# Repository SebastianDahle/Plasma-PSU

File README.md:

View this project on [CADLAB.io](https://cadlab.io/project/22638). 

# Plasma-PSU
Semi-professional HV power supply for various plasma applications, including Gliding Arcs, Dielectric Barrier Discharges, or School demonstrations. The design shall be suited for use in a laboratory environment, but simple and cheap to allow for uptake in DIY communities.

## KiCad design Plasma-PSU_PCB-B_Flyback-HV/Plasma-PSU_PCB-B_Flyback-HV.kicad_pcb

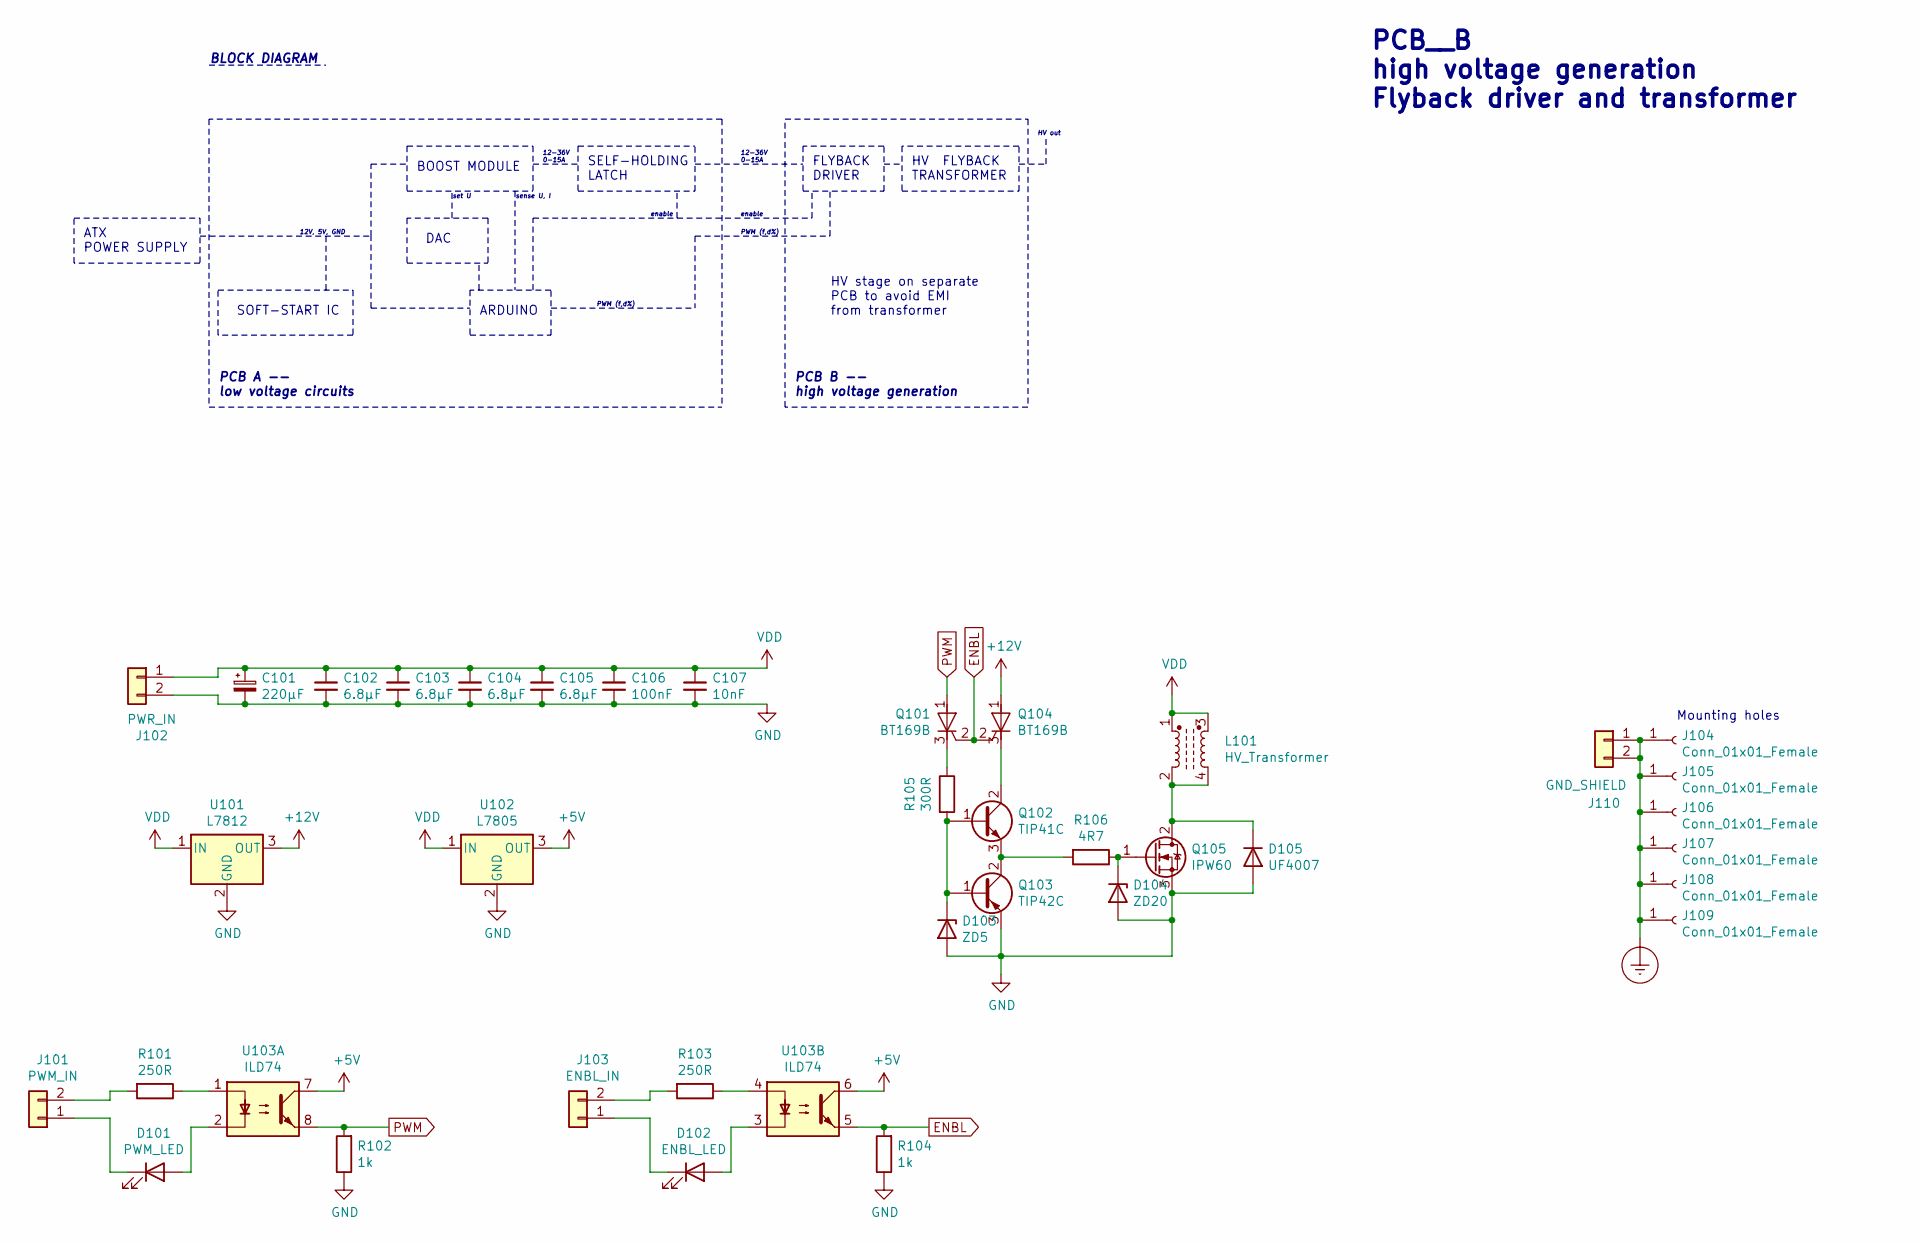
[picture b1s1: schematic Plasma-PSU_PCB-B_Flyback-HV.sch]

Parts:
C101: 220µF; CP_Radial_D8.0mm_P3.50mm
C102, C103, C104, C105: 6.8µF; C_Disc_D6.0mm_W2.5mm_P5.00mm
C106: 100nF; C_1206_3216Metric
C107: 10nF; C_0805_2012Metric
D101: PWM_LED; LED_0603_1608Metric
D102: ENBL_LED; LED_0603_1608Metric
D103: ZD5; D_DO-41_SOD81_P7.62mm_Horizontal
D104: ZD20; D_DO-41_SOD81_P7.62mm_Horizontal
D105: UF4007; D_DO-41_SOD81_P7.62mm_Horizontal
J101: PWM_IN; PinHeader_1x02_P2.54mm_Vertical
J102: PWR_IN; TerminalBlock_Phoenix_MKDS-3-2-5.08_1x02_P5.08mm_Horizontal
J103: ENBL_IN; PinHeader_1x02_P2.54mm_Vertical
J104, J105, J106, J107, J108, J109: Conn_01x01_Female; MountingHole_3.2mm_M3_Pad_Via
J110: GND_SHIELD; TerminalBlock_Phoenix_MKDS-3-2-5.08_1x02_P5.08mm_Horizontal
L101: HV_Transformer; HF-HV_Transformer_15kV_300W
Q101, Q104: BT169B; TO-92_Inline
Q102: TIP41C; TO-220-3_Vertical
Q103: TIP42C; TO-220-3_Vertical
Q105: IPW60; TO-247-3_Vertical
R101, R103: 250R; R_0603_1608Metric
R102, R104: 1k; R_0603_1608Metric
R105: 300R; R_0603_1608Metric
R106: 4R7; R_Axial_DIN0207_L6.3mm_D2.5mm_P7.62mm_Horizontal
U101: L7812; TO-220-3_Vertical
U102: L7805; TO-220-3_Vertical
U103: ILD74; DIP-8_W7.62mm

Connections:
+5V: U102.3 (OUT), U103.6, U103.7
+12V: Q104.1 (A), U101.3 (OUT)
ENBL: Q101.2 (G), Q104.2 (G), R104.2, U103.5
Earth_Protective: J104.1, J105.1, J106.1, J107.1, J108.1, J109.1, J110.1, J110.2
GND: C101.2, C102.2, C103.2, C104.2, C105.2, C106.2, C107.2, D103.2 (A), D104.2 (A), D105.2 (A), J102.2, Q103.3 (E), Q105.3 (S), R102.1, R104.1, U101.2 (GND), U102.2 (GND)
unnamed: D101.1 (K), J101.1
unnamed: D101.2 (A), U103.2
unnamed: D102.1 (K), J103.1
unnamed: D102.2 (A), U103.3
unnamed: D103.1 (K), Q102.1 (B), Q103.1 (B), R105.2
unnamed: D104.1 (K), Q105.1 (G), R106.1
unnamed: D105.1 (K), L101.2, L101.4, Q105.2 (D)
unnamed: J101.2, R101.2
unnamed: J103.2, R103.2
unnamed: Q101.3 (K), R105.1
unnamed: Q102.2 (C), Q104.3 (K)
unnamed: Q102.3 (E), Q103.2 (C), R106.2
unnamed: R101.1, U103.1
unnamed: R103.1, U103.4
PWM: Q101.1 (A), R102.2, U103.8
VDD: C101.1, C102.1, C103.1, C104.1, C105.1, C106.1, C107.1, J102.1, L101.1, L101.3, U101.1 (IN), U102.1 (IN)

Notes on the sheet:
HV stage on separate PCB to avoid EMI from transformer
PCB__B high voltage generation Flyback driver and transformer
ATX POWER SUPPLY
SOFT-START IC
BOOST MODULE
ARDUINO
DAC
FLYBACK DRIVER
HV FLYBACK TRANSFORMER
set U
sense U, I
12-36V 0-15A
PWM (f,d%)
HV out
PCB A -- low voltage circuits
PCB B -- high voltage generation
BLOCK DIAGRAM
SELF-HOLDING LATCH
enable
12V, 5V, GND
Mounting holes

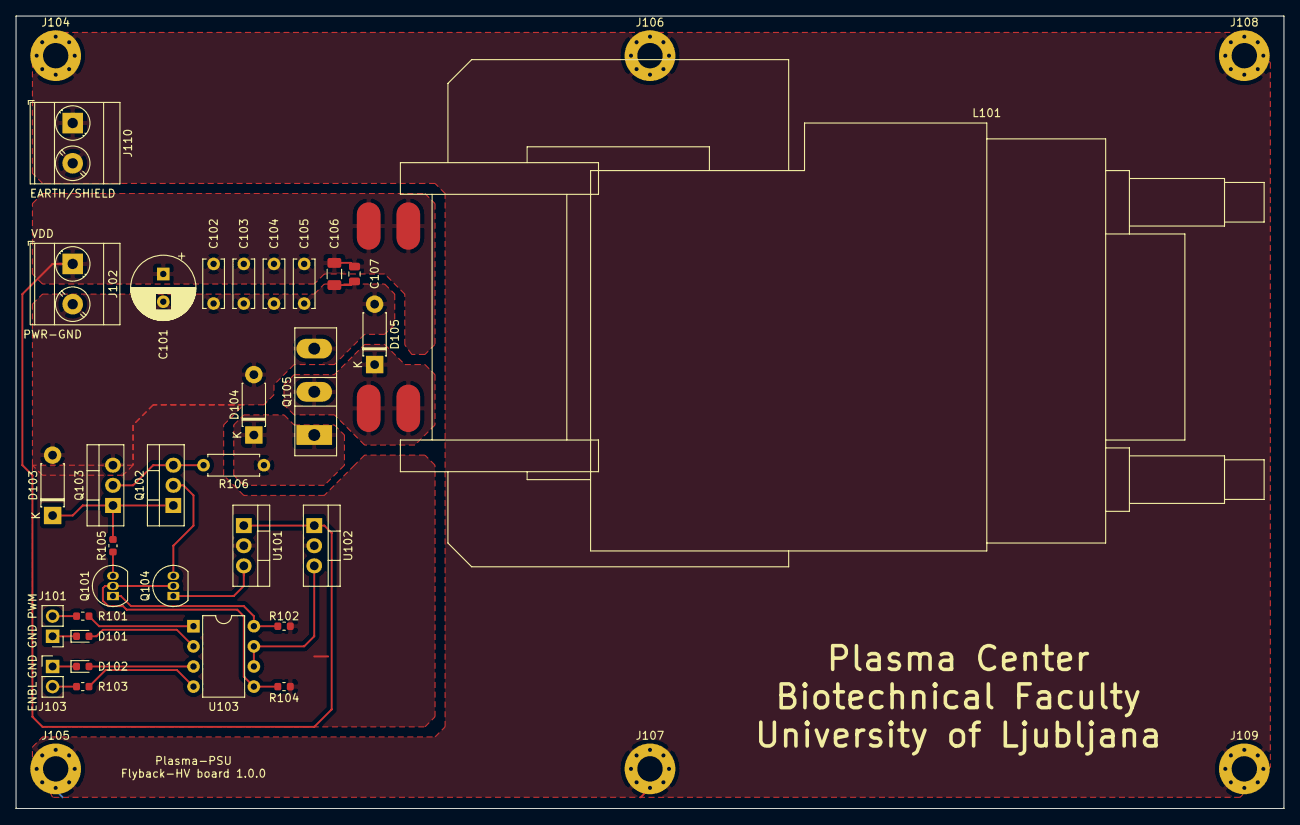
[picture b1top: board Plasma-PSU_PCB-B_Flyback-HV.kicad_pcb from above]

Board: 2 copper layers, 160.0 x 100.0 mm, 37 parts (0 on the bottom side), 21 nets.

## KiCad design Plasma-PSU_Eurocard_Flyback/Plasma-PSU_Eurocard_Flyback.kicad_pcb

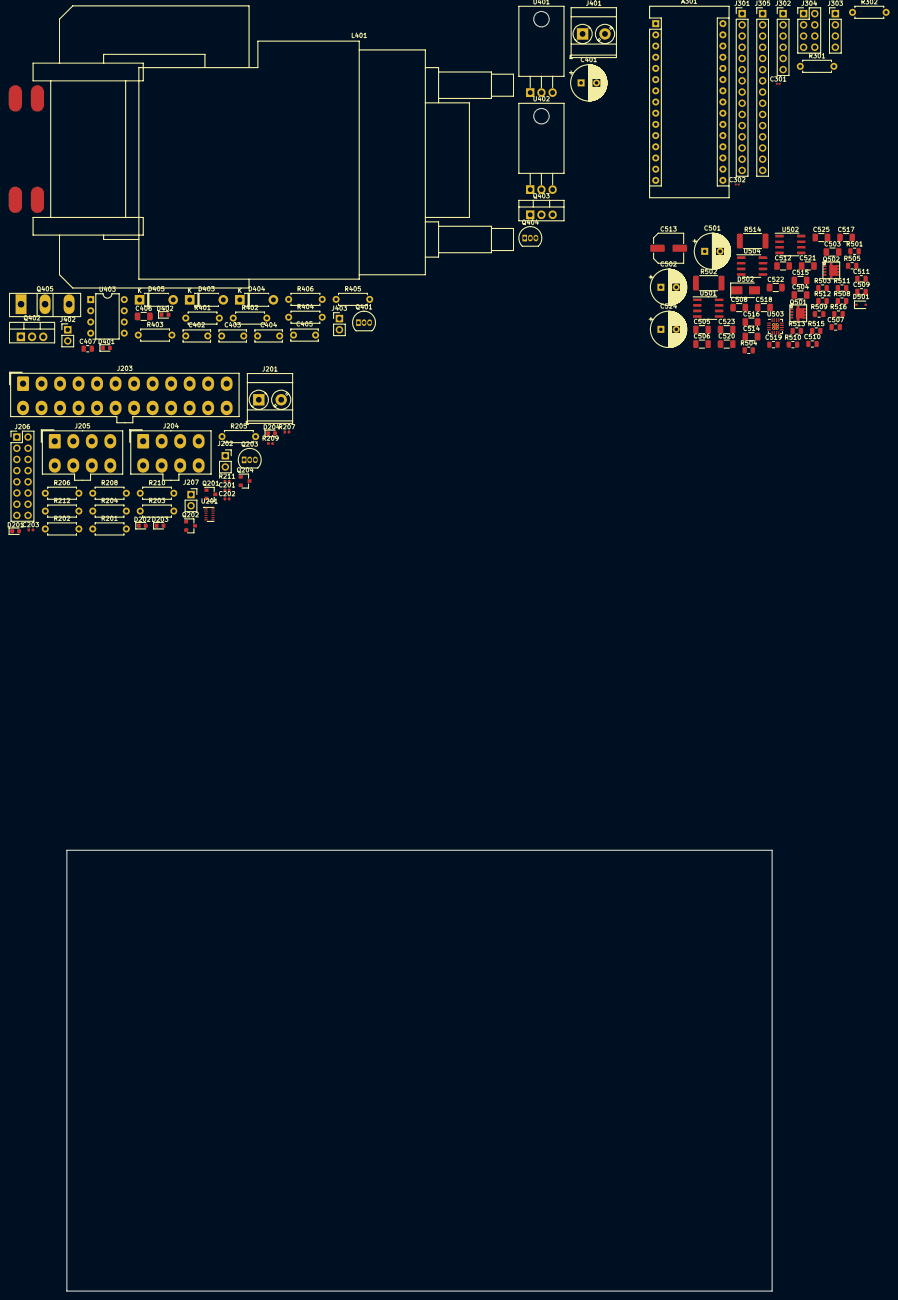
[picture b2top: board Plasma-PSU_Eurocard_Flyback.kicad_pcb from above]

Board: 2 copper layers, 160.0 x 100.0 mm, 118 parts (0 on the bottom side), 100 nets, no tracks yet.

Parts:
A301: Arduino_Nano_v3.x; Arduino_Nano
C201, C203: 1µF; C_0402_1005Metric
C202: 100nF; C_0402_1005Metric
C301, C302: 100n; C_0201_0603Metric
C401: 220µF; CP_Radial_D8.0mm_P3.50mm
C402, C403, C404, C405: 6.8µF; C_Disc_D6.0mm_W2.5mm_P5.00mm
C406, C505, C506, C508, C512, C514, C515, C516, C518, C520, C525: 100nF; C_1206_3216Metric
C407, C507, C509, C519: 10nF; C_0805_2012Metric
C501, C502, C524: 220uF; CP_Radial_D8.0mm_P3.50mm
C503, C504, C521, C522, C523: 6.8µF; C_1206_3216Metric
C510: 15nF; C_0805_2012Metric
C511: 220pF; C_0805_2012Metric
C513: 10µF; C_Elec_6.3x5.8
C517: 4.7µ MLCC; C_1206_3216Metric
D201, D202, D203, D204: LED; LED_0603_1608Metric
D401: PWM_LED; LED_0603_1608Metric
D402: ENBL_LED; LED_0603_1608Metric
D403: ZD5; D_DO-41_SOD81_P7.62mm_Horizontal
D404: ZD20; D_DO-41_SOD81_P7.62mm_Horizontal
D405: UF4007; D_DO-41_SOD81_P7.62mm_Horizontal
D501: ZD5; D_SOD-323
D502: B120-E3; D_SMA
J201: PWR_FWD; TerminalBlock_Phoenix_MKDS-3-2-5.08_1x02_P5.08mm_Horizontal
J202: PWM_FWD; PinSocket_1x02_P2.54mm_Vertical
J203: Molex Mini-fit Jr. 39-28-1243; Molex_Mini-Fit_Jr_5566-24A_2x12_P4.20mm_Vertical
J204, J205: Molex Mini-fit Jr. 39-28-1083; Molex_Mini-Fit_Jr_5566-08A_2x04_P4.20mm_Vertical
J206: Pinheader Controls; PinHeader_2x08_P2.54mm_Vertical
J207: ENBL_FWD; PinSocket_1x02_P2.54mm_Vertical
J301: Arduino_Pinout_01-15; PinHeader_1x15_P2.54mm_Vertical
J302: SPI; PinHeader_1x06_P2.54mm_Vertical
J303: UART; PinHeader_1x04_P2.54mm_Vertical
J304: I2C; PinHeader_2x04_P2.54mm_Vertical
J305: Arduino_Pinout_16-30; PinHeader_1x15_P2.54mm_Vertical
J401: PWR_IN; TerminalBlock_Phoenix_MKDS-3-2-5.08_1x02_P5.08mm_Horizontal
J402: PWM_IN; PinHeader_1x02_P2.54mm_Vertical
J403: ENBL_IN; PinHeader_1x02_P2.54mm_Vertical
L401: HV_Transformer; HF-HV_Transformer_15kV_300W
Q201, Q202: BC818; SOT-23
Q203, Q401, Q404: BT169B; TO-92_Inline
Q204: BC808; SOT-23
Q402: TIP41C; TO-220-3_Vertical
Q403: TIP42C; TO-220-3_Vertical
Q405: IPW60; TO-247-3_Vertical
Q501, Q502: NVTFS6H850NL; ONSEMI-µ8FL
R201, R202, R203, R204: 10k; R_Axial_DIN0207_L6.3mm_D2.5mm_P7.62mm_Horizontal
R205: 470R; R_Axial_DIN0207_L6.3mm_D2.5mm_P7.62mm_Horizontal
R206, R208, R210, R212, R403, R404: 1k; R_Axial_DIN0207_L6.3mm_D2.5mm_P7.62mm_Horizontal
R207, R209, R211: 470R; R_0402_1005Metric
R301, R302: 4.8k; R_Axial_DIN0207_L6.3mm_D2.5mm_P7.62mm_Horizontal
R401, R402: 250R; R_Axial_DIN0207_L6.3mm_D2.5mm_P7.62mm_Horizontal
R405: 300R; R_Axial_DIN0207_L6.3mm_D2.5mm_P7.62mm_Horizontal
R406: 4R7; R_Axial_DIN0207_L6.3mm_D2.5mm_P7.62mm_Horizontal
R501: 8.66k; R_0805_2012Metric
R502: 2mR; R_2512_6332Metric
R503, R504, R505, R508, R512, R516: 100k; R_0805_2012Metric
R509: 34k; R_0805_2012Metric
R510: 2k; R_0805_2012Metric
R511: 4.8k; R_0805_2012Metric
R513, R515: 3.3k; R_0805_2012Metric
R514: 1mR (2512); R_2512_6332Metric
U201: STM6600; TDFN-12_2x3mm_P0.5mm
U401: L7812; TO-220-3_Horizontal_TabDown
U402: L7805; TO-220-3_Horizontal_TabDown
U403: ILD74; DIP-8_W7.62mm
U501, U502: MCP602; SOIC-8_3.9x4.9mm_P1.27mm
U503: LTC3786; QFN-16-1EP_3x3mm_P0.5mm_EP1.45x1.45mm_ThermalVias
U504: MCP4822; SOIC-8_3.9x4.9mm_P1.27mm

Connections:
+3V3: J203.1, J203.2, J203.12, J203.13
+5V: A301.30, C501.1, C508.1, C509.1, C513.1, C514.1, J203.4, J203.6, J203.21, J203.22, J203.23, J206.5, J302.2, J303.3, J304.5, J304.6, J305.15, Q202.3, R201.1, R202.1, R204.1, U501.8, U502.8, U504.1
+12V: C502.1, C503.1, C504.1, C505.1, C506.1, C507.1, C515.2, J203.10, J203.11, J204.1, J204.2, J204.3, J205.1, J205.2, J205.3, R502.2, U503.2, U503.12
/Controller/D13_16: A301.16, J302.6, J305.1, U504.3
/Controller/I-Sense_IN: R301.2, R512.1, U502.1
/Controller/RES_3: A301.3, J301.3
/Controller/SPI-CS: A301.8, J301.8, U504.2
/Controller/SPI-MISO: A301.15, J301.15, J302.5
/Controller/SPI-MOSI: A301.14, J301.14, J302.4, U504.4
/Controller/U-Sense_IN: R302.2, U502.6, U502.7
/Flyback_HV_stage/+5V: U402.3, U403.6, U403.7
/Flyback_HV_stage/+12V: Q404.1, U401.3
/Flyback_HV_stage/ENBL: Q401.2, Q404.2, R404.2, U403.5
/Flyback_HV_stage/GND: C401.2, C402.2, C403.2, C404.2, C405.2, C406.2, C407.2, D403.2, D404.2, D405.2, J401.1, Q403.3, Q405.3, R403.1, R404.1, U401.2, U402.2
/Flyback_HV_stage/PWM: Q401.1, R403.2, U403.8
/Flyback_HV_stage/VDD: C401.1, C402.1, C403.1, C404.1, C405.1, C406.1, C407.1, J401.2, L401.1, U401.1, U402.1
/Plugs_and_Controls/ENBL_A: A301.12, D501.1, J206.7, J301.12, U503.8
/Plugs_and_Controls/ENBL_JP: J206.10, Q202.1, R208.2
/Plugs_and_Controls/GND_IN: J201.2, R514.1
/Plugs_and_Controls/PB: J206.1, U201.6
/Plugs_and_Controls/PLASMA_OFF: J206.15, Q204.3, R211.2
/Plugs_and_Controls/PLASMA_ON: J206.13, J207.1, Q203.3, Q204.1, R209.2, R210.2
/Plugs_and_Controls/PWM_IN: A301.11, J202.1, J301.11
/Plugs_and_Controls/PWR_GOOD: J203.8, R207.2, U201.4
/Plugs_and_Controls/PWR_ON: J203.16, Q201.3
/Plugs_and_Controls/SR: J206.3, U201.2
/Plugs_and_Controls/START_BTN: J206.6, R205.2
/Plugs_and_Controls/STOP_BTN: J206.8, J206.9
/Plugs_and_Controls/VDD_IN: C519.1, C520.1, C521.1, C522.1, C523.1, C524.1, J201.1, Q502.3, R509.2, R511.2
/Plugs_and_Controls/VSB: C202.1, J203.9, R203.1, U201.1
/SMPS-12-36/U-Sense_int: R509.1, R510.2, U501.3
/SMPS-12-36/VFB: R508.1, U501.7, U503.1
GND: A301.4, A301.29, C201.2, C202.2, C203.2, C301.1, C302.2, C501.2, C502.2, C503.2, C504.2, C505.2, C506.2, C507.2, C508.2, C509.2, C510.1, C511.1, C512.1, C513.2, C514.2, C515.1, C517.1, C518.2, C519.2, C520.2, C521.2, C522.2, C523.2, C524.2, C525.2, D202.1, D203.1, D204.1, D501.2, J202.2, J203.3, J203.5, J203.7, J203.15, J203.17, J203.18, J203.19, J203.24, J204.5, J204.7, J204.8, J205.5, J205.7, J205.8, J206.2, J206.4, J206.12, J206.14, J206.16, J207.2, J301.4, J302.1, J303.4, J304.7, J304.8, J305.14, Q201.2, Q501.1, R206.1, R208.1, R210.1, R212.1, R510.1, R516.1, U201.12, U501.4, U502.4, U503.6, U503.7, U503.9, U504.5, U504.7
unnamed: A301.1, J301.1, J303.2
unnamed: A301.2, J301.2, J303.1
unnamed: A301.5, J301.5
unnamed: A301.6, J301.6
unnamed: A301.7, J301.7
unnamed: A301.9, J301.9
unnamed: A301.10, J301.10
unnamed: A301.13, J301.13, J302.3
unnamed: A301.17, J305.2
unnamed: A301.18, J305.3
unnamed: A301.19, J305.4
unnamed: A301.20, J305.5
unnamed: A301.21, J305.6
unnamed: A301.22, J305.7
unnamed: A301.23, J304.3, J304.4, J305.8
unnamed: A301.24, J304.1, J304.2, J305.9
unnamed: A301.25, C302.1, J305.10, R302.1
unnamed: A301.26, C301.2, J305.11, R301.1
unnamed: A301.27, J305.12
unnamed: A301.28, J305.13
unnamed: C201.1, U201.5
unnamed: C203.1, U201.3
unnamed: C510.2, R501.1
unnamed: C511.2, R501.2, U503.4
unnamed: C512.2, U503.5
unnamed: C516.1, Q501.3, Q502.1, U503.15
unnamed: C516.2, D502.1, U503.13
unnamed: C517.2, D502.2, R503.2, U503.11
unnamed: C518.1, R505.1, U501.5
unnamed: C525.1, R511.1, U502.5
unnamed: D201.1, U201.7
unnamed: D201.2, R203.2
unnamed: D202.2, R207.1
unnamed: D203.2, R209.1
unnamed: D204.2, R211.1
unnamed: D401.1, J402.1
unnamed: D401.2, U403.2
unnamed: D402.1, J403.1
unnamed: D402.2, U403.3
unnamed: D403.1, Q402.1, Q403.1, R405.2
unnamed: D404.1, Q405.1, R406.1
unnamed: D405.1, L401.2, Q405.2
unnamed: J402.2, R401.2
unnamed: J403.2, R402.2
unnamed: R502.1, U503.3
unnamed: Q201.1, U201.9
unnamed: Q202.2, Q203.1
unnamed: Q203.2, R205.1, R206.2
unnamed: Q204.2, R212.2
unnamed: Q401.3, R405.1
unnamed: Q402.2, Q404.3
unnamed: Q402.3, Q403.2, R406.2
unnamed: Q501.2, U503.10
unnamed: Q502.2, U503.14
unnamed: R201.2, U201.11
unnamed: R202.2, U201.10
unnamed: R204.2, U201.8
unnamed: R401.1, U403.1
unnamed: R402.1, U403.4
unnamed: R503.1, U503.16
unnamed: R504.1, U501.2
unnamed: R504.2, U504.8
unnamed: R505.2, U504.6
unnamed: R508.2, U501.1, U501.6
unnamed: R512.2, R513.2, U502.2
unnamed: R514.2, R515.2
unnamed: R515.1, R516.2, U502.3

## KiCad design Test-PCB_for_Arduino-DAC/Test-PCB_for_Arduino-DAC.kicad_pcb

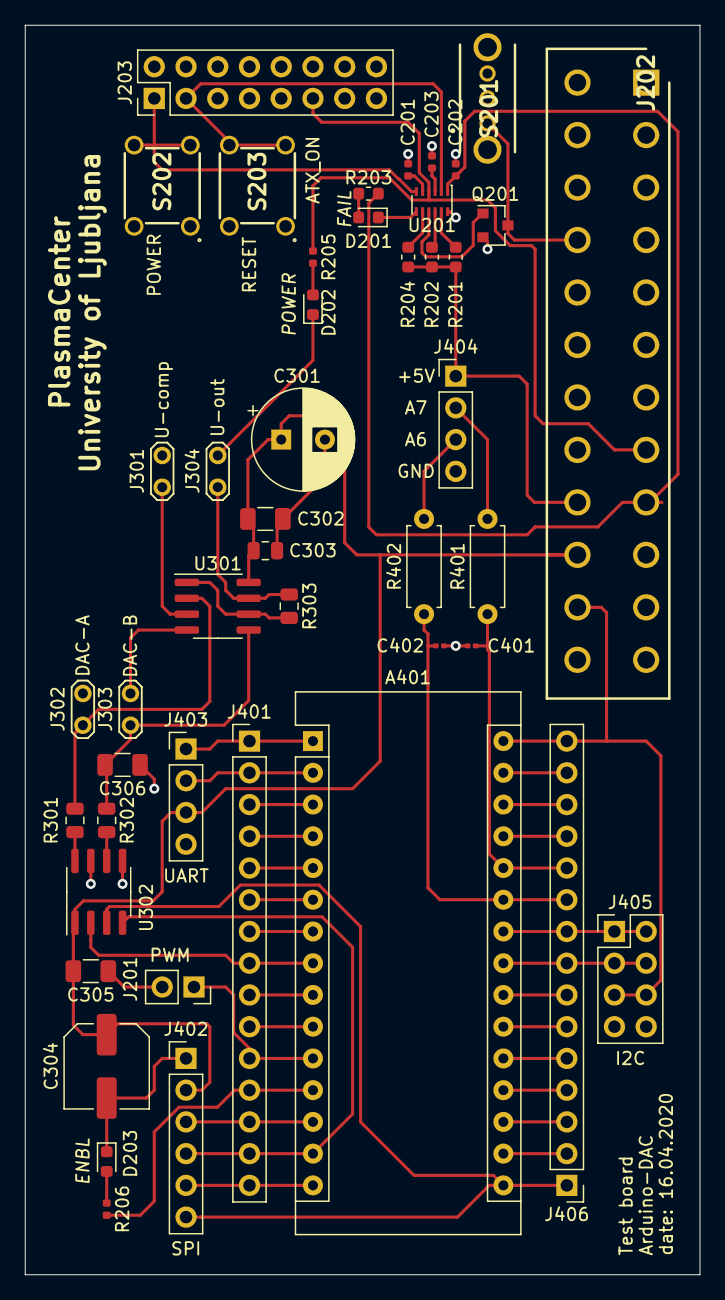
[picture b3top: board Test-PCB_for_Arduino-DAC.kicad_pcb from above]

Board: 2 copper layers, 54.0 x 100.0 mm, 46 parts (0 on the bottom side), 55 nets.

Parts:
A401: Arduino_Nano_v3.x; Arduino_Nano
C201, C203: 1µF; C_0402_1005Metric
C202: 100nF; C_0402_1005Metric
C301: 220uF; CP_Radial_D8.0mm_P3.50mm
C302, C305, C306: 100nF; C_1206_3216Metric
C303: 10nF; C_0805_2012Metric
C304: 10µF; C_Elec_6.3x5.8
C401, C402: 100n; C_0201_0603Metric
D201, D202, D203: LED; LED_0603_1608Metric
J201: PWM_FWD; PinSocket_1x02_P2.54mm_Vertical
J202: 39-28-1243; SHDR24W120P550X420_2X12_5160X960X1310P
J203: Pinheader Controls; PinHeader_2x08_P2.54mm_Vertical
J301: U-Sense_int; TestPoint_2Pads_Pitch2.54mm_Drill0.8mm
J302: Probe_DAC_A; TestPoint_2Pads_Pitch2.54mm_Drill0.8mm
J303: Probe_DAC_B; TestPoint_2Pads_Pitch2.54mm_Drill0.8mm
J304: VFB; TestPoint_2Pads_Pitch2.54mm_Drill0.8mm
J401: Arduino_Pinout_01-15; PinHeader_1x15_P2.54mm_Vertical
J402: SPI; PinHeader_1x06_P2.54mm_Vertical
J403: UART; PinHeader_1x04_P2.54mm_Vertical
J404: A6+7; PinHeader_1x04_P2.54mm_Vertical
J405: I2C; PinHeader_2x04_P2.54mm_Vertical
J406: Arduino_Pinout_16-30; PinHeader_1x15_P2.54mm_Vertical
Q201: BC818; SOT-23
R201, R202, R203, R204: 10k; R_0603_1608Metric
R205, R206: 470R; R_0402_1005Metric
R301, R302, R303: 100k; R_0805_2012Metric
R401, R402: 4.8k; R_Axial_DIN0207_L6.3mm_D2.5mm_P7.62mm_Horizontal
S201: OS102011MS2QN1; OS102011MA1QN1
S202, S203: 1825910-6
U201: STM6600; TDFN-12_2x3mm_P0.5mm
U301: MCP602; SOIC-8_3.9x4.9mm_P1.27mm
U302: MCP4822; SOIC-8_3.9x4.9mm_P1.27mm

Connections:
+3V3: J202.1, J202.2, J202.3, J202.23
+5V: A401.30, C301.1, C302.1, C303.1, C304.1, C305.1, J202.7, J202.11, J202.18, J202.20, J202.22, J402.2, J403.3, J404.1, J405.5, J405.6, J406.15, R201.1, R202.1, R204.1, U301.8, U302.1
+12V: J202.19, J202.21
/Controller/D13_16: A401.16, J402.6, J406.1, U302.3
/Controller/RES_3: A401.3, J401.3
/Controller/SPI-CS: A401.8, J401.8, U302.2
/Controller/SPI-MISO: A401.15, J401.15, J402.5
/Controller/SPI-MOSI: A401.14, J401.14, J402.4, U302.4
/Plugs_and_Controls/ENBL: A401.12, J401.12, R206.2
/Plugs_and_Controls/PB: J203.1, S202.3, S202.4, U201.6
/Plugs_and_Controls/PWM_IN: A401.11, J201.1, J401.11
/Plugs_and_Controls/PWR_GOOD: J202.15, J203.11, R205.2, U201.4
/Plugs_and_Controls/PWR_ON: J202.8, Q201.3, S201.1
/Plugs_and_Controls/SR: J203.3, S203.3, S203.4, U201.2
/Plugs_and_Controls/VSB: C202.1, J202.17, R203.1, U201.1
GND: A401.4, A401.29, C201.2, C202.2, C203.2, C301.2, C302.2, C303.2, C304.2, C305.2, C306.2, C401.1, C402.2, D202.1, D203.1, J201.2, J202.5, J202.6, J202.9, J202.10, J202.12, J202.13, J202.14, J202.24, J203.2, J203.4, J203.12, J203.14, J203.16, J301.2, J302.2, J303.2, J304.2, J401.4, J402.1, J403.4, J404.4, J405.7, J405.8, J406.14, Q201.2, S201.2, S201.3, S202.1, S202.2, S203.1, S203.2, U201.12, U301.4, U302.5, U302.7
unnamed: A401.1, J401.1, J403.1
unnamed: A401.2, J401.2, J403.2
unnamed: A401.5, J401.5
unnamed: A401.6, J401.6
unnamed: A401.7, J401.7
unnamed: A401.9, J401.9
unnamed: A401.10, J401.10
unnamed: A401.13, J401.13, J402.3
unnamed: A401.17, J406.2
unnamed: A401.18, J406.3
unnamed: A401.19, J406.4
unnamed: A401.20, J406.5
unnamed: A401.21, J406.6
unnamed: A401.22, J406.7
unnamed: A401.23, J405.3, J405.4, J406.8
unnamed: A401.24, J405.1, J405.2, J406.9
unnamed: A401.25, C402.1, J406.10, R402.1
unnamed: A401.26, C401.2, J406.11, R401.1
unnamed: A401.27, J406.12
unnamed: A401.28, J406.13
unnamed: C201.1, U201.5
unnamed: C203.1, U201.3
unnamed: C306.1, J303.1, R302.1, U301.5
unnamed: D201.1, U201.7
unnamed: D201.2, R203.2
unnamed: D202.2, R205.1
unnamed: D203.2, R206.1
unnamed: J301.1, U301.3
unnamed: J302.1, R301.1, U301.2
unnamed: J304.1, R303.1, U301.7
unnamed: J404.2, R401.2
unnamed: J404.3, R402.2
unnamed: Q201.1, U201.9
unnamed: R201.2, U201.11
unnamed: R202.2, U201.10
unnamed: R204.2, U201.8
unnamed: R301.2, U302.8
unnamed: R302.2, U302.6
unnamed: R303.2, U301.1, U301.6

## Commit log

2020-03-20 Backlink to CADLAB.io has been added.
2020-04-06 Intro Eurocard & Arduino
    - Construction step towards circuit on 2x Euroboard PCB
    - Replacing Ruideng DVS by own boost circuit
    - Introducing Arduino as controller
2020-04-06 Include LTC3786 regulator IC
2020-04-06 LTC3786 arranged according to datasheet
2020-04-06 Filter caps & Rsense revised
2020-04-07 Block diagram, Connectivity, Isolation
    - First page reservered for block diagram
    - Connectors moved to separate sheet
    - Opto-isolators for signal inputs on HV board
    - Fuse added to SMPS
    - Pinheader for Arduino pin-out, UART, I2C, SPI
2020-04-07 STM6600 power-up included
    An STM6600 IC is now used to enable stand-by and touch-button operation
2020-04-07 Block diagram included
2020-04-08 Filters for sense signals
    - RC filters on U-sense and I-sense included
    - Block diagram refined
2020-04-08 DAC sets U_out
    DAC converter in SMPS sheet sets boost modules output voltage.
2020-04-08 Datasheets included
2020-04-08 SMPS & Shunt selected
2020-04-08 Footprints added
    All footprints included, except:
    - Boost Inductor
    - 60A fuse holder
2020-04-11 Testpoints & SMPS jumper included
2020-04-11 KiCad files split into PCB-A and PCB-B
    - PCB-A remains with controller & smps as was, but renamed as ./Plasma-PSU_PCB-A_Power-Controller
    - PCB-B, namely the HV generation, is moved into ./Plasma-PSU_PCB-B_Flyback-HV
    - PCB tracing created for PCB-B
2020-04-12 Flyback PCB w/ SMD & Earth
    - Changed most resistors to SMD
    - Included Earth planes separate from GND for shielding
2020-04-12 Gerber files Flyback-HV for inquiry
2020-04-16 BOM PCB-B arranged
    Order numbers for Farnell-element14 and for Mouser
2020-04-16 Power Inductor updated
2020-04-16 Test-PCB created for Arduino+DAC
    Separate test board created, on which the following parts will be tested:
    - Arduino
    - DAC
    - OP AMP
    - Soft-start IC
    - ATX 24pin power connector
2020-04-16 Improved Test-PCB Arduino-DAC
2020-04-17 FET & L revision w/ LTpowerCAD
    LTpowerCAD tool used to revise selection of:
    - main inductor
    - control FET
    - sync FET
    - input and output capacitor banks
2020-04-17 Datasheets updated

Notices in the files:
Plasma-PSU_PCB-B_Flyback-HV/Plasma-PSU_PCB-B_Flyback-HV.sch:
This work is licensed under a Creative Commons Attribution 3.0 Unported License
